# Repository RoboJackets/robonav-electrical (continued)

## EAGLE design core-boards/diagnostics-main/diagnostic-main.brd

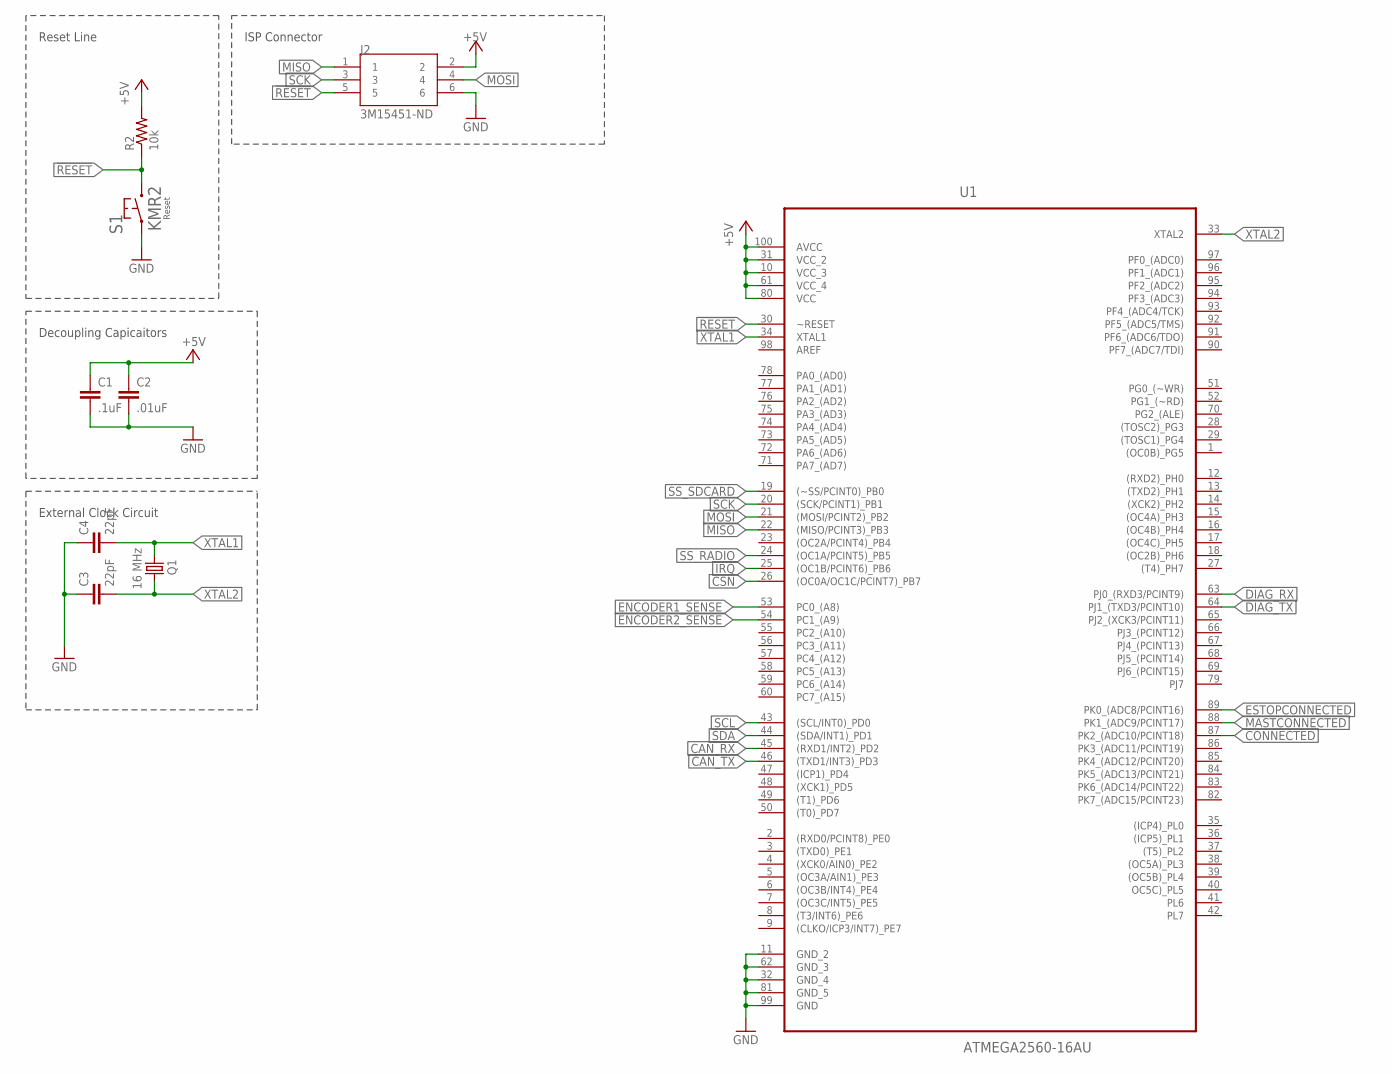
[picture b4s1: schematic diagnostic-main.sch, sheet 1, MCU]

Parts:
C1: .1uF; C0603
C2: .01uF; C0603
C3, C4: 22pF; C0603
J2: 3M15451-ND; 3M_30306-6002HB
Q1: 16 MHz; CSM-7X-DU
R2: 10k; R0402
S1: KMR2
U1: ATMEGA2560-16AU; QFP50P1600X1600X120-100N

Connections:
!RESET: J2.5, R2.1, S1.2.1 (2), S1.2.2 (2), U1.30 (~RESET)
+5V: C1.1, C2.1, J2.2, R2.2, U1.10 (VCC_3), U1.31 (VCC_2), U1.61 (VCC_4), U1.80 (VCC), U1.100 (AVCC); also elsewhere on the board
CAN_RX: U1.45 ((RXD1/INT2)_PD2); also elsewhere on the board
CAN_TX: U1.46 ((TXD1/INT3)_PD3); also elsewhere on the board
CONNECTED: U1.87 (PK2_(ADC10/PCINT18)); also elsewhere on the board
CSN: U1.26 ((OC0A/OC1C/PCINT7)_PB7); also elsewhere on the board
DIAG_RX: U1.63 (PJ0_(RXD3/PCINT9)); also elsewhere on the board
DIAG_TX: U1.64 (PJ1_(TXD3/PCINT10)); also elsewhere on the board
ENCODER1_SENSE: U1.53 (PC0_(A8)); also elsewhere on the board
ENCODER2_SENSE: U1.54 (PC1_(A9)); also elsewhere on the board
ESTOPCONNECTED: U1.89 (PK0_(ADC8/PCINT16)); also elsewhere on the board
GND: C1.2, C2.2, C3.1, C4.1, J2.6, S1.1.1 (1), S1.1.2 (1), U1.11 (GND_2), U1.32 (GND_4), U1.62 (GND_3), U1.81 (GND_5), U1.99 (GND); also elsewhere on the board
IRQ: U1.25 ((OC1B/PCINT6)_PB6); also elsewhere on the board
MASTCONNECTED: U1.88 (PK1_(ADC9/PCINT17)); also elsewhere on the board
MISO: J2.1, U1.22 ((MISO/PCINT3)_PB3); also elsewhere on the board
MOSI: J2.4, U1.21 ((MOSI/PCINT2)_PB2); also elsewhere on the board
SCK: J2.3, U1.20 ((SCK/PCINT1)_PB1); also elsewhere on the board
SCL: U1.43 ((SCL/INT0)_PD0)
SDA: U1.44 ((SDA/INT1)_PD1)
SS_RADIO: U1.24 ((OC1A/PCINT5)_PB5); also elsewhere on the board
SS_SDCARD: U1.19 ((~SS/PCINT0)_PB0); also elsewhere on the board
XTAL1: C4.2, Q1.1, U1.34 (XTAL1)
XTAL2: C3.2, Q1.2, U1.33 (XTAL2)

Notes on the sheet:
Reset Line
External Clock Circuit
Decoupling Capicaitors
ISP Connector

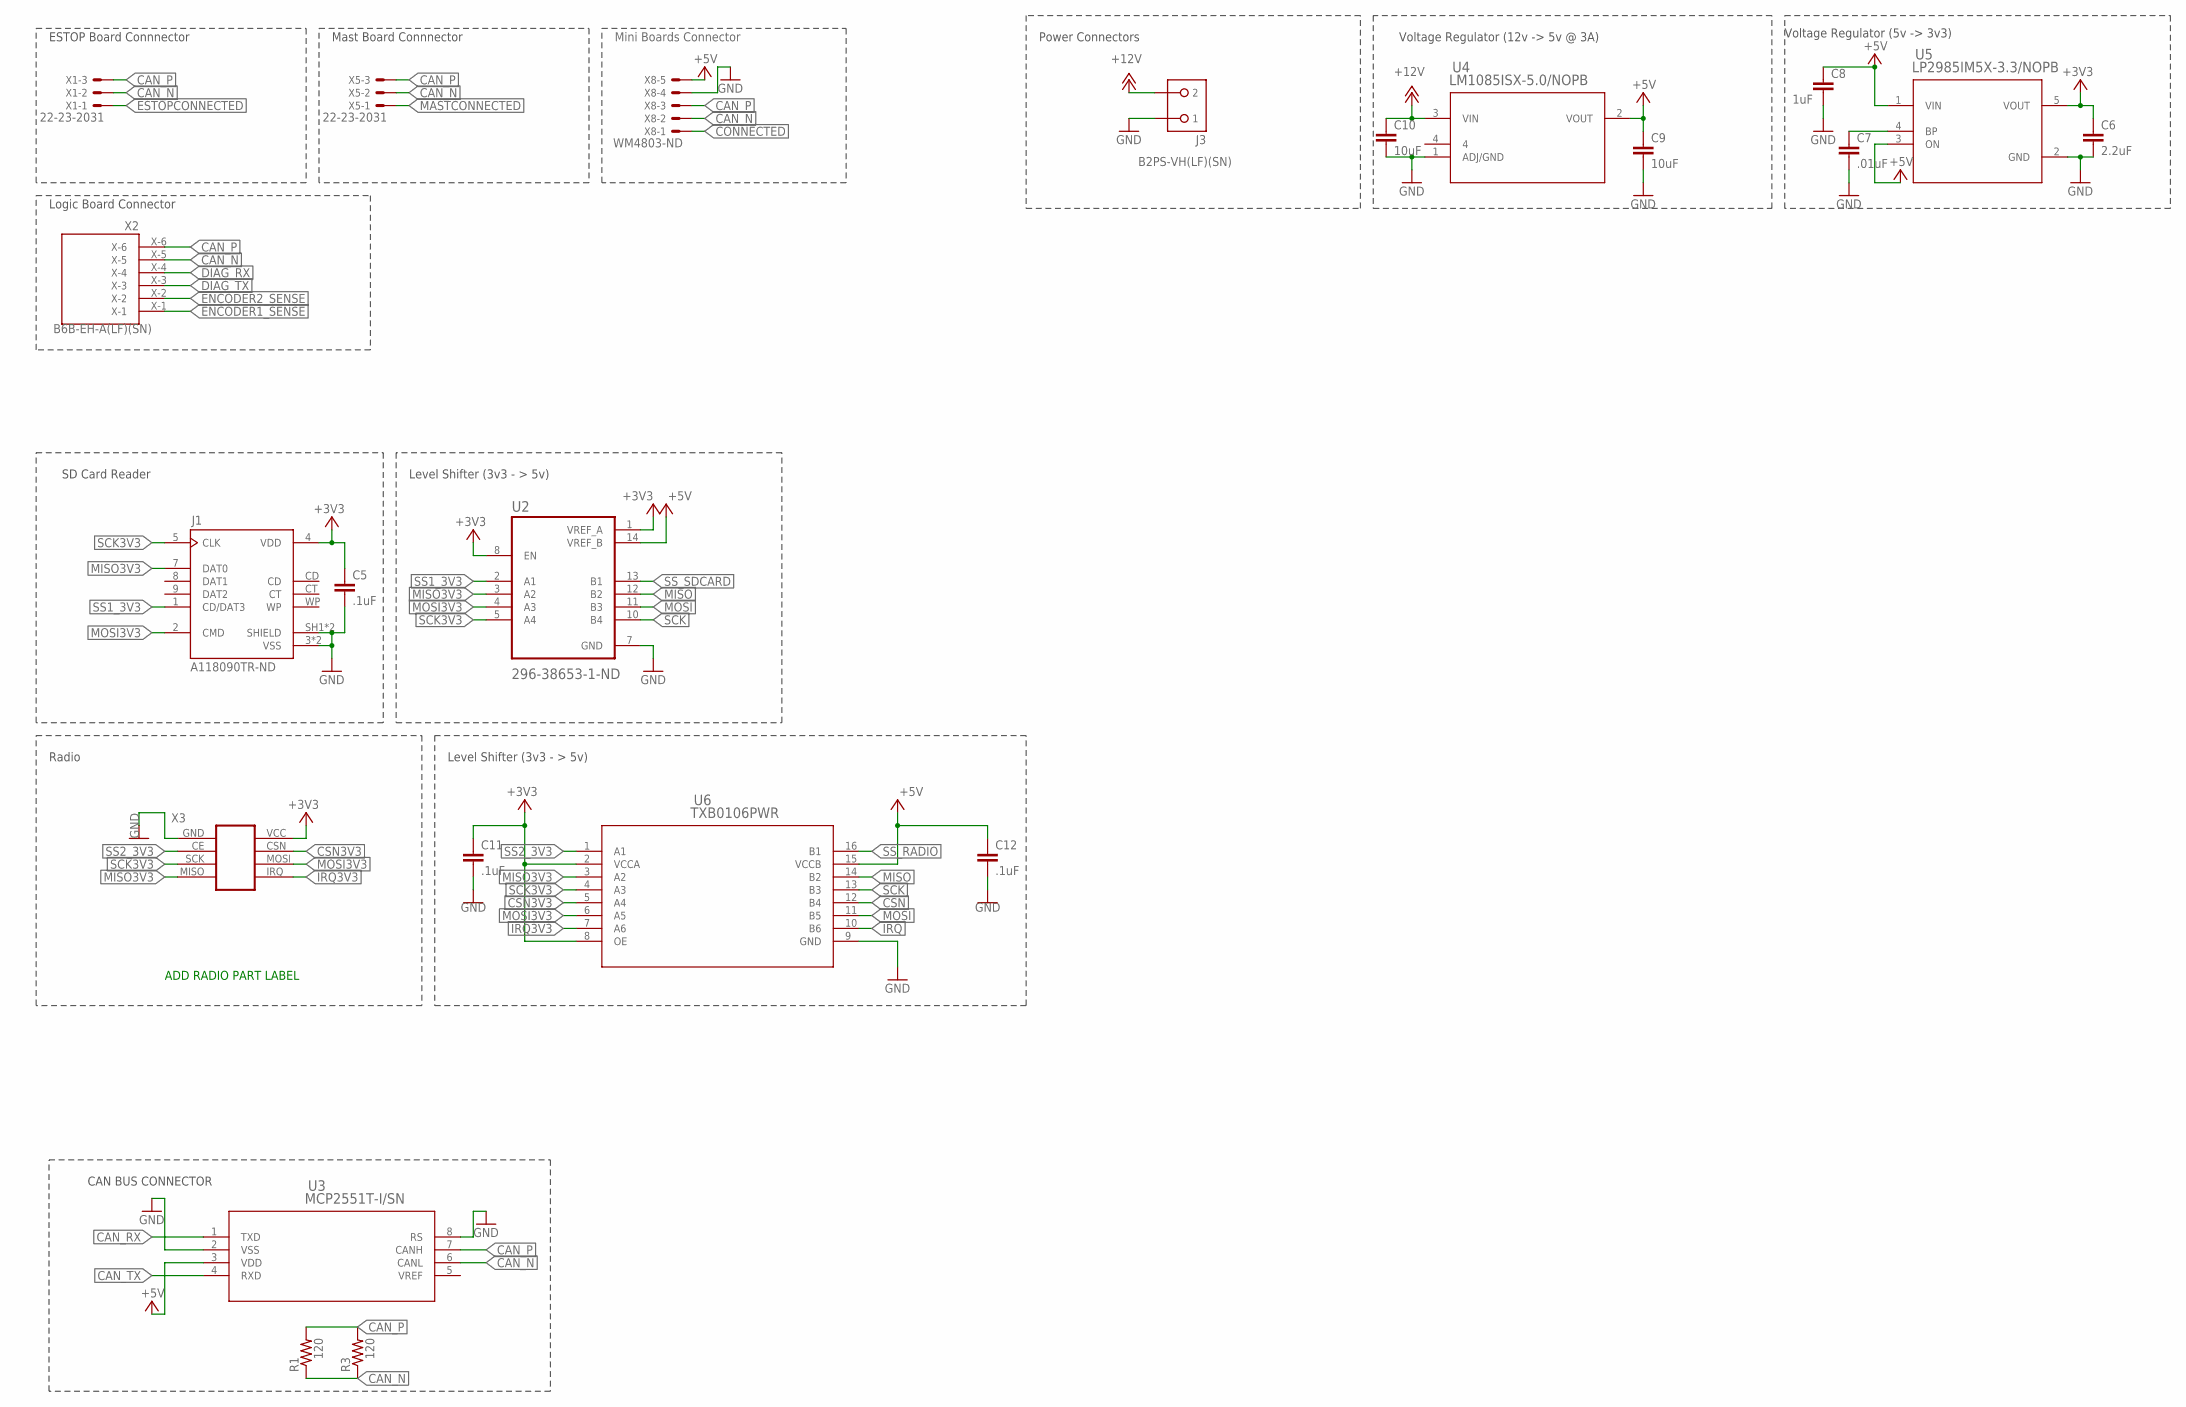
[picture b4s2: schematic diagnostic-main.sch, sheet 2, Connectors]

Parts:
C5, C11, C12: .1uF; C0603
C6: 2.2uF; C0603
C7: .01uF; C0603
C8: 1uF; C0603
C9, C10: 10uF; C0805
J1: A118090TR-ND; TE_1939870-1
J3: B2PS-VH(LF)(SN); B2PS-CENTERED
R1, R3: 120; R0402
U2: 296-38653-1-ND; SOP65P640X120-14N
U3: MCP2551T-I/SN; SOIC8-N_MC
U4: LM1085ISX-5.0/NOPB; TS3B
U5: LP2985IM5X-3.3/NOPB; MF05A
U6: TXB0106PWR; PW16
X1, X5: 22-23-2031
X2: B6B-EH-A(LF)(SN); B6BEHALFSN
X3: NRF24L01+PA+LNA
X8: WM4803-ND; 22-23-2051

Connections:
+3V3: C5.1, C6.1, C11.1, J1.4 (VDD), U2.1 (VREF_A), U2.8 (EN), U5.5 (VOUT), U6.2 (VCCA), U6.8 (OE), X3.VCC
+5V: C8.1, C9.1, C12.1, U2.14 (VREF_B), U3.3 (VDD), U4.2 (VOUT), U5.1 (VIN), U5.3 (ON), U6.15 (VCCB), X8.5; also elsewhere on the board
+12V: C10.1, J3.2, U4.3 (VIN)
CAN_N: R1.1, R3.1, U3.6 (CANL), X1.2, X2.X-5, X5.2, X8.2
CAN_P: R1.2, R3.2, U3.7 (CANH), X1.3, X2.X-6, X5.3, X8.3
CAN_RX: U3.1 (TXD); also elsewhere on the board
CAN_TX: U3.4 (RXD); also elsewhere on the board
CONNECTED: X8.1; also elsewhere on the board
CSN: U6.12 (B4); also elsewhere on the board
CSN3V3: U6.5 (A4), X3.CSN
DIAG_RX: X2.X-4; also elsewhere on the board
DIAG_TX: X2.X-3; also elsewhere on the board
ENCODER1_SENSE: X2.X-1; also elsewhere on the board
ENCODER2_SENSE: X2.X-2; also elsewhere on the board
ESTOPCONNECTED: X1.1; also elsewhere on the board
GND: C5.2, C6.2, C7.2, C8.2, C9.2, C10.2, C11.2, C12.2, J1.3 (VSS), J1.6 (VSS), J1.SH1 (SHIELD), J1.SH2 (SHIELD), J3.1, U2.7 (GND), U3.2 (VSS), U3.8 (RS), U4.1 (ADJ/GND), U5.2 (GND), U6.9 (GND), X3.GND, X8.4; also elsewhere on the board
IRQ: U6.10 (B6); also elsewhere on the board
IRQ3V3: U6.7 (A6), X3.IRQ
MASTCONNECTED: X5.1; also elsewhere on the board
MISO: U2.12 (B2), U6.14 (B2); also elsewhere on the board
MISO3V3: J1.7 (DAT0), U2.3 (A2), U6.3 (A2), X3.MISO
MOSI: U2.11 (B3), U6.11 (B5); also elsewhere on the board
MOSI3V3: J1.2 (CMD), U2.4 (A3), U6.6 (A5), X3.MOSI
unnamed: C7.1, U5.4 (BP)
SCK: U2.10 (B4), U6.13 (B3); also elsewhere on the board
SCK3V3: J1.5 (CLK), U2.5 (A4), U6.4 (A3), X3.SCK
SS1_3V3: J1.1 (CD/DAT3), U2.2 (A1)
SS2_3V3: U6.1 (A1), X3.CE
SS_RADIO: U6.16 (B1); also elsewhere on the board
SS_SDCARD: U2.13 (B1); also elsewhere on the board

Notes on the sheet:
ESTOP Board Connnector
SD Card Reader
Level Shifter (3v3 - > 5v)
Logic Board Connector
Mini Boards Connector
CAN BUS CONNECTOR
Voltage Regulator (12v -> 5v @ 3A)
Voltage Regulator (5v -> 3v3)
Power Connectors
Radio
Mast Board Connnector
ADD RADIO PART LABEL

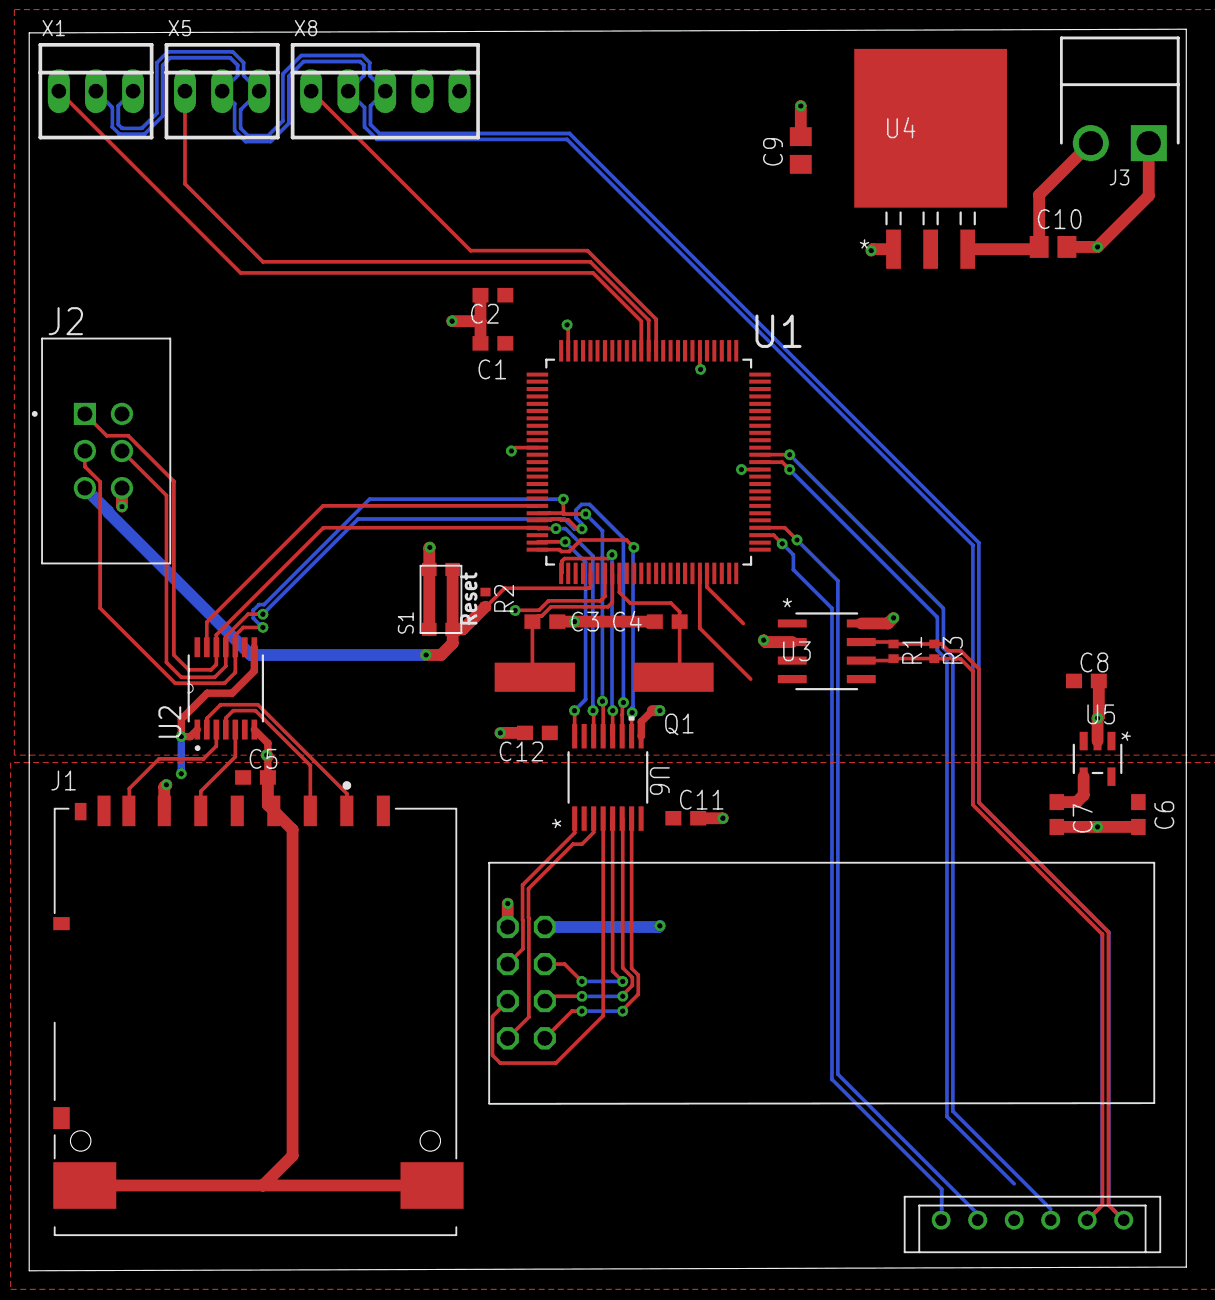
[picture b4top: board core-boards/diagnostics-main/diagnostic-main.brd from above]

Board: 2 copper layers, 79.2 x 85.0 mm, 31 parts (0 on the bottom side), 33 nets.

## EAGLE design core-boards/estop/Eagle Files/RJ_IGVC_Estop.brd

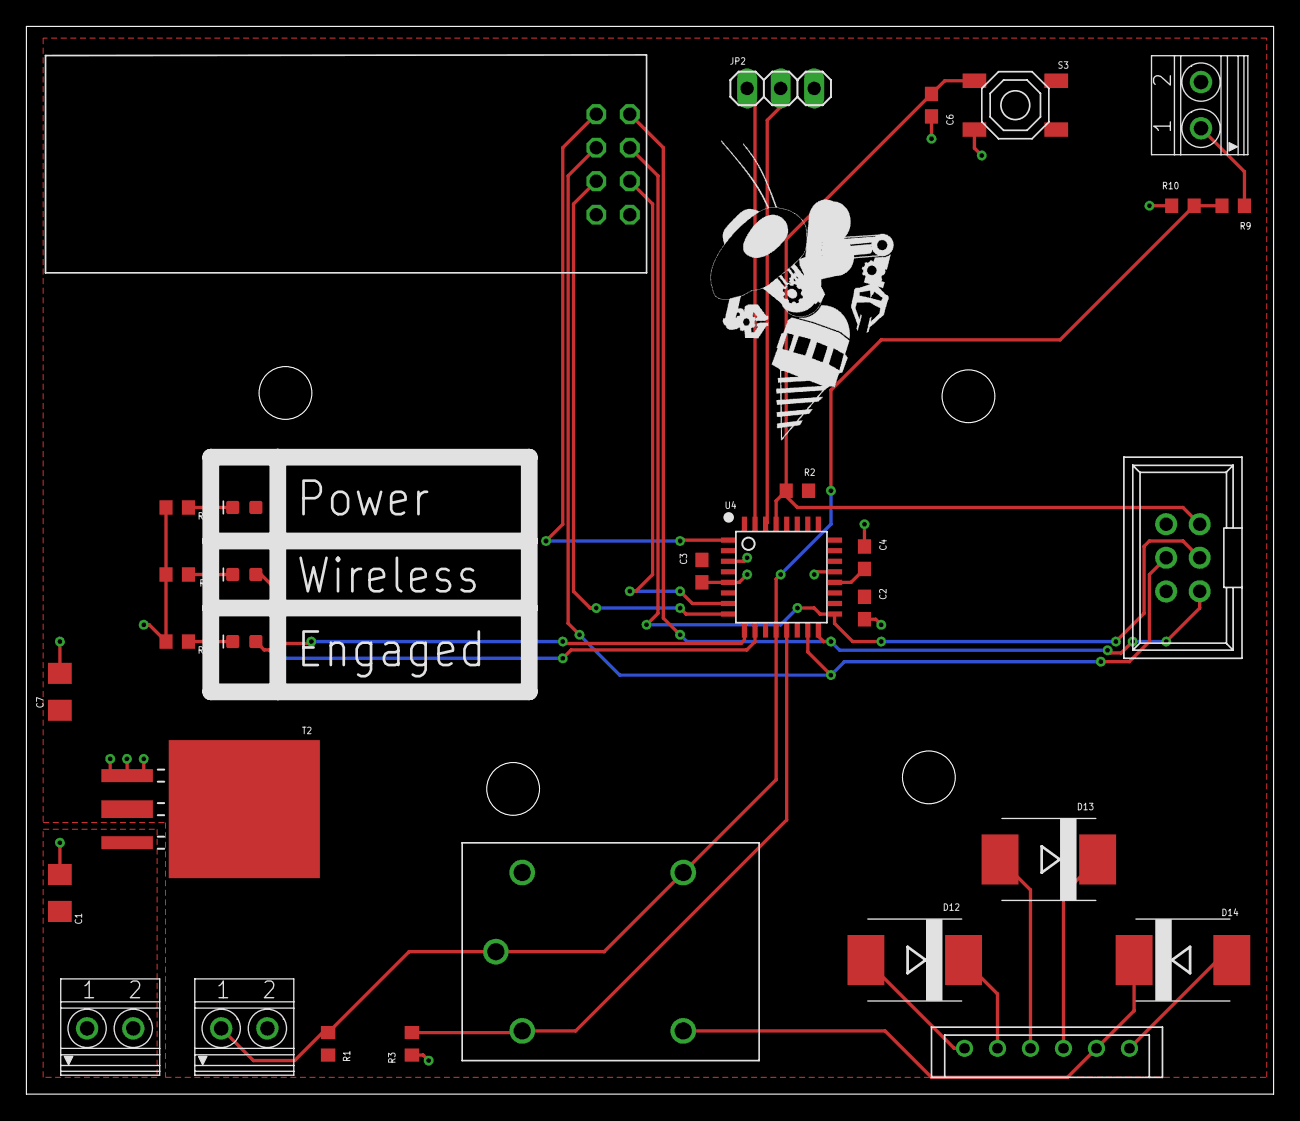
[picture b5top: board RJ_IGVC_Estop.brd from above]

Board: 2 copper layers, 94.5 x 80.9 mm, 32 parts (0 on the bottom side), 26 nets.

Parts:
C1, C7: 10uF; C1206
C2, C3, C4, C6: 0.1uF; C0603
D1, D2, D3: Green; LED-0603
D12, D13, D14: S10M-TP; SMC
JP2: Serial; 1X03
PROG: ICSP Connector; 2X3SHROUDED
R1, R2, R3: 10k; R0603
R4, R5, R6: 1k; R0603
R9: 4.7k; R0603
R10: 750; R0603
S3: SKQGADE010; SW4-SMD-5.2X5.2X1.5MM
T2: LD1086D2M33TR; D2PAK/A
U4: ATMEGA328P-AUR
U$1: G5LE-14
U$2: ROBOBUZZ_1.2X
X2: Power; 1751248
X3: Button In; 1751248
X4: E-Stop Signal In; 1751248
X5: NRF24L01+PA+LNA
X6: B6B-EH-A(LF)(SN); B6BEHALFSN

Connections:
!RESET: C6.1, PROG.!RESET, R2.1, S3.1, U4.29
+3V3: C2.1, C3.1, C7.1, D2.A, PROG.+5V, R1.1, R2.2, T2.2, U4.4, U4.6, U4.18, X5.VCC
+24V: D12.A, X6.X-1
BUTTON_LED: D1.A, U4.9
CE: U4.7, X5.CE
CSN: U4.8, X5.CSN
DIODE_TO_GREEN: D12.C, X6.X-2
DIODE_TO_INTER: D13.C, X6.X-4
GND: C1.2, C2.2, C3.2, C4.2, C6.2, C7.2, D14.A, JP2.3, PROG.GND, R3.1, R4.1, R5.1, R6.1, R10.2, S3.4, T2.1, U4.3, U4.5, U4.21, U$1.P$1, X2.2, X3.2, X4.2, X5.GND, X6.X-6
IN: R1.2, R9.2, R10.1, U4.12, U$1.P$2, U$1.P$4, X3.1
IRQ: U4.1, X5.IRQ
MISO: PROG.MISO, U4.16, X5.MISO
MOSI: PROG.MOSI, U4.15, X5.MOSI
MOTOR_POWER: D13.A, X6.X-3
unnamed: D2.C, R5.2
unnamed: D1.C, R4.2
unnamed: D3.C, R6.2
unnamed: R9.1, X4.1
unnamed: C4.1, U4.20
OUT: R3.2, U4.13, U$1.P$3
RX: JP2.2, U4.30
SCK: PROG.SCK, U4.17, X5.SCK
SOLENOID_TRIG: D14.C, U$1.P$5, X6.X-5
TX: JP2.1, U4.31
V_IN: C1.1, T2.3, X2.1
WIRELESS_LED: D3.A, U4.10

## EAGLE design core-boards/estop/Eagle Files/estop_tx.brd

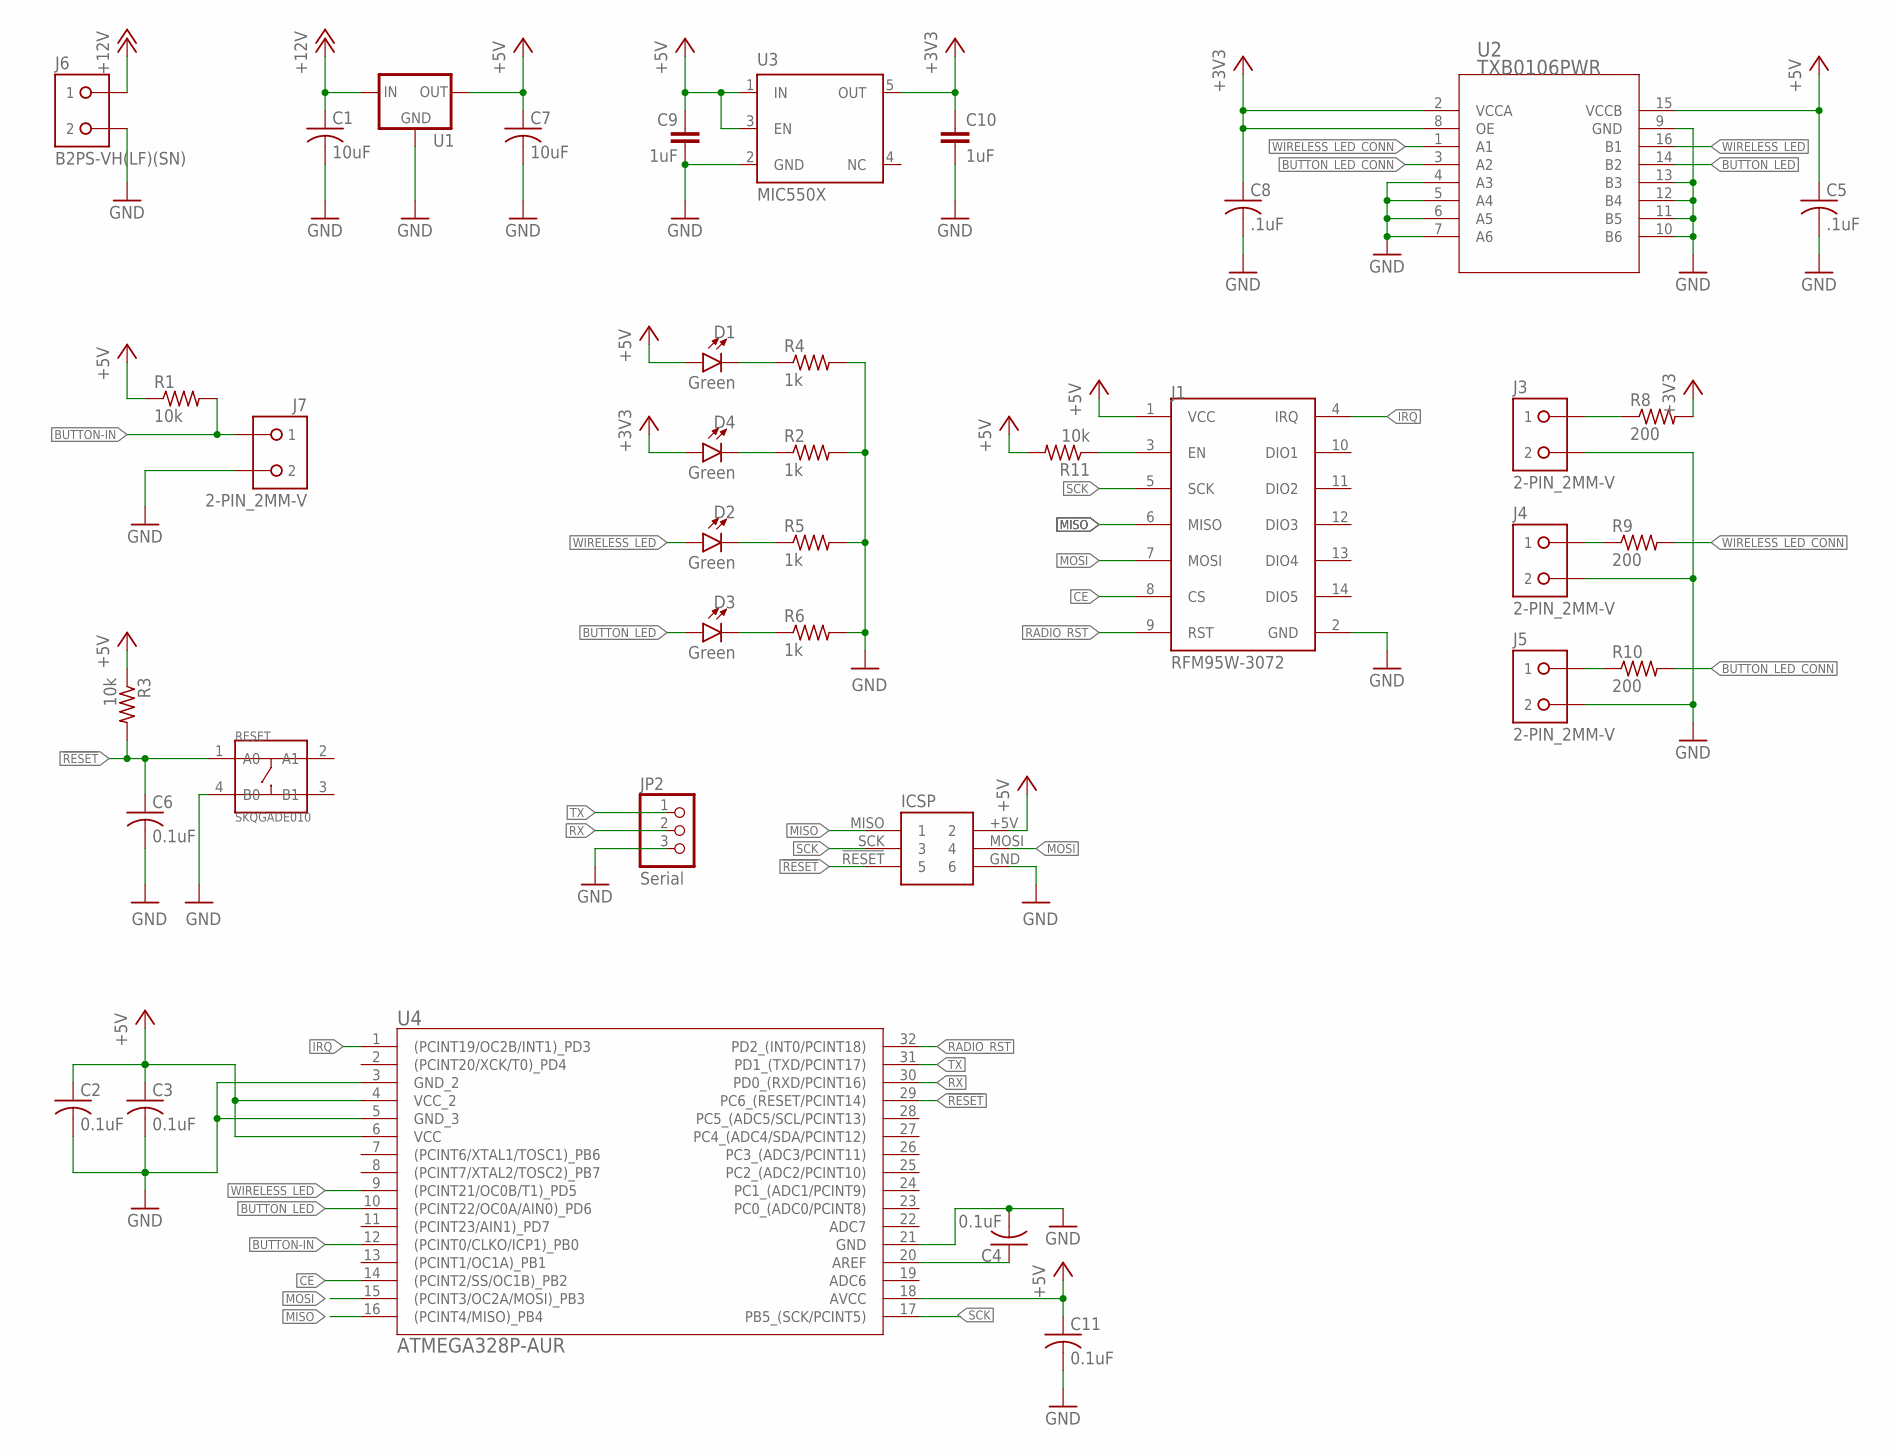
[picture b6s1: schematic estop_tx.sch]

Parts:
C1, C7: 10uF; C0805
C2, C3, C4, C6, C11: 0.1uF; C0603
C5, C8: .1uF; C0603
C9, C10: 1uF; C0603
D1, D2, D3, D4: Green; LED-0603
ICSP: ICSP Connector; 2X3SHROUDED
J1: RFM95W-3072
J3, J4, J5, J7: 2-PIN_2MM-V; 2MM-2-V
J6: B2PS-VH(LF)(SN); B2PS-CENTERED
JP2: Serial; 1X03
R1, R3, R11: 10k; R0603
R2, R4, R5, R6: 1k; R0603
R8, R9, R10: 200; R0603
RESET: SKQGADE010; SW4-SMD-5.2X5.2X1.5MM
U1: R-78E5.0-1.0CONV_R-78E5.0-1.0; CONV_R-78E5.0-1.0
U2: TXB0106PWR; PW16
U3: MIC550X; SOT23-DBV
U4: ATMEGA328P-AUR

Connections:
!RESET: C6.1, ICSP.!RESET (5), R3.2, RESET.1 (A0), U4.29 (PC6_(RESET/PCINT14))
+3V3: C8.1, C10.1, D4.A, R8.2, U2.2 (VCCA), U2.8 (OE), U3.5 (OUT)
+5V: C2.1, C3.1, C5.1, C7.1, C9.1, C11.1, D1.A, ICSP.+5V (2), J1.1 (VCC), R1.1, R3.1, R11.2, U1.3 (OUT), U2.15 (VCCB), U3.1 (IN), U3.3 (EN), U4.4 (VCC_2), U4.6 (VCC), U4.18 (AVCC)
+12V: C1.1, J6.1, U1.1 (IN)
BUTTON-IN: J7.1, R1.2, U4.12 ((PCINT0/CLKO/ICP1)_PB0)
BUTTON_LED: D3.A, U2.14 (B2), U4.10 ((PCINT22/OC0A/AIN0)_PD6)
BUTTON_LED_CONN: R10.2, U2.3 (A2)
CE: J1.8 (CS), U4.14 ((PCINT2/SS/OC1B)_PB2)
EN: J1.3 (EN), R11.1
GND: C1.2, C2.2, C3.2, C4.2, C5.2, C6.2, C7.2, C8.2, C9.2, C10.2, C11.2, ICSP.GND (6), J1.2 (GND), J3.2, J4.2, J5.2, J6.2, J7.2, JP2.3, R2.2, R4.2, R5.2, R6.2, RESET.4 (B0), U1.2 (GND), U2.4 (A3), U2.5 (A4), U2.6 (A5), U2.7 (A6), U2.9 (GND), U2.10 (B6), U2.11 (B5), U2.12 (B4), U2.13 (B3), U3.2 (GND), U4.3 (GND_2), U4.5 (GND_3), U4.21 (GND)
IRQ: J1.4 (IRQ), U4.1 ((PCINT19/OC2B/INT1)_PD3)
MISO: ICSP.MISO (1), J1.6 (MISO), U4.16 ((PCINT4/MISO)_PB4)
MOSI: ICSP.MOSI (4), J1.7 (MOSI), U4.15 ((PCINT3/OC2A/MOSI)_PB3)
unnamed: J3.1, R8.1
unnamed: D1.C, R4.1
unnamed: D3.C, R6.1
unnamed: D2.C, R5.1
unnamed: D4.C, R2.1
unnamed: J4.1, R9.1
unnamed: J5.1, R10.1
unnamed: C4.1, U4.20 (AREF)
RADIO_RST: J1.9 (RST), U4.32 (PD2_(INT0/PCINT18))
RX: JP2.2, U4.30 (PD0_(RXD/PCINT16))
SCK: ICSP.SCK (3), J1.5 (SCK), U4.17 (PB5_(SCK/PCINT5))
TX: JP2.1, U4.31 (PD1_(TXD/PCINT17))
WIRELESS_LED: D2.A, U2.16 (B1), U4.9 ((PCINT21/OC0B/T1)_PD5)
WIRELESS_LED_CONN: R9.2, U2.1 (A1)

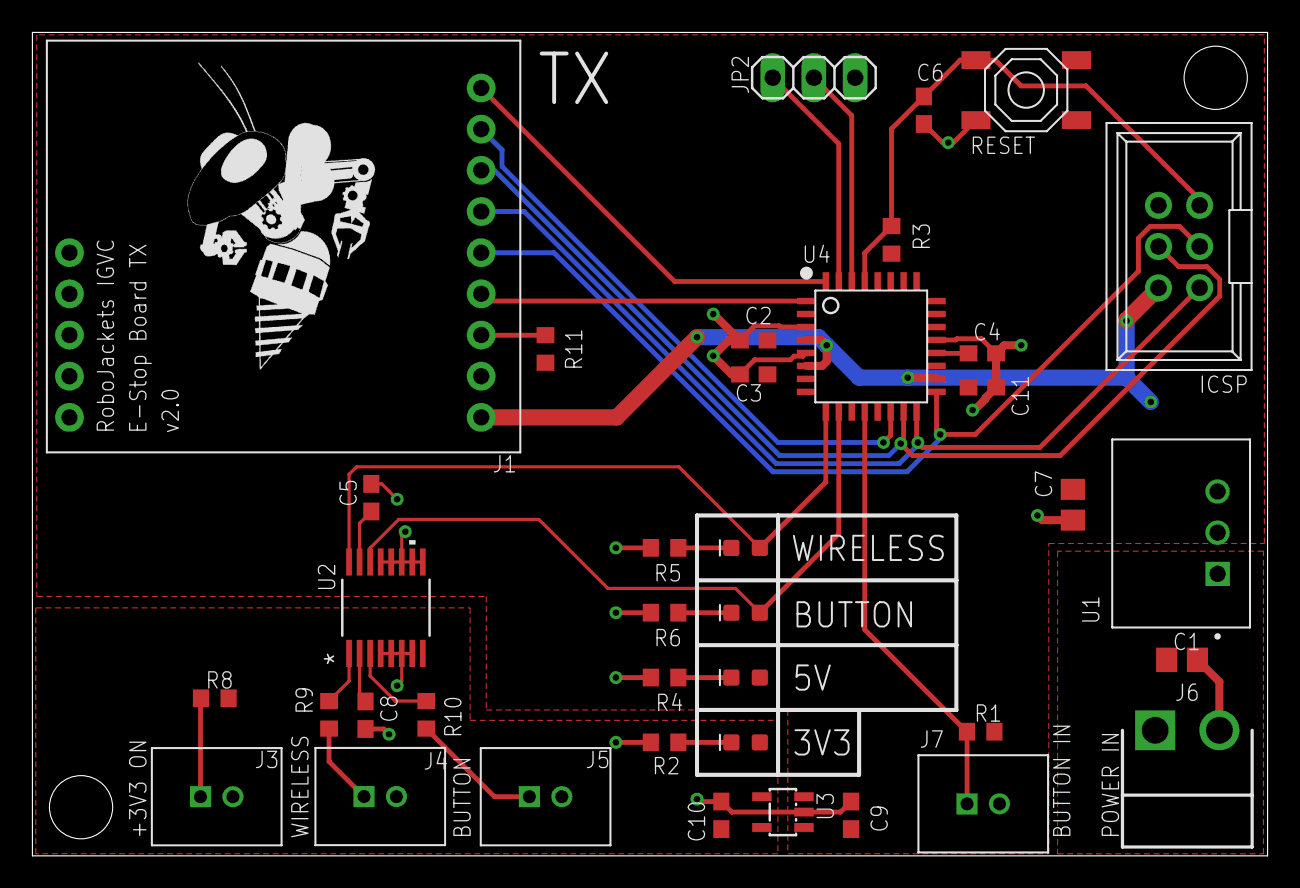
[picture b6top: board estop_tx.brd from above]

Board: 2 copper layers, 76.2 x 50.8 mm, 41 parts (0 on the bottom side), 27 nets.

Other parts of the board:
U$1: ROBOBUZZ_1.0X
U$2, U$3: STANDOFF-HOLE

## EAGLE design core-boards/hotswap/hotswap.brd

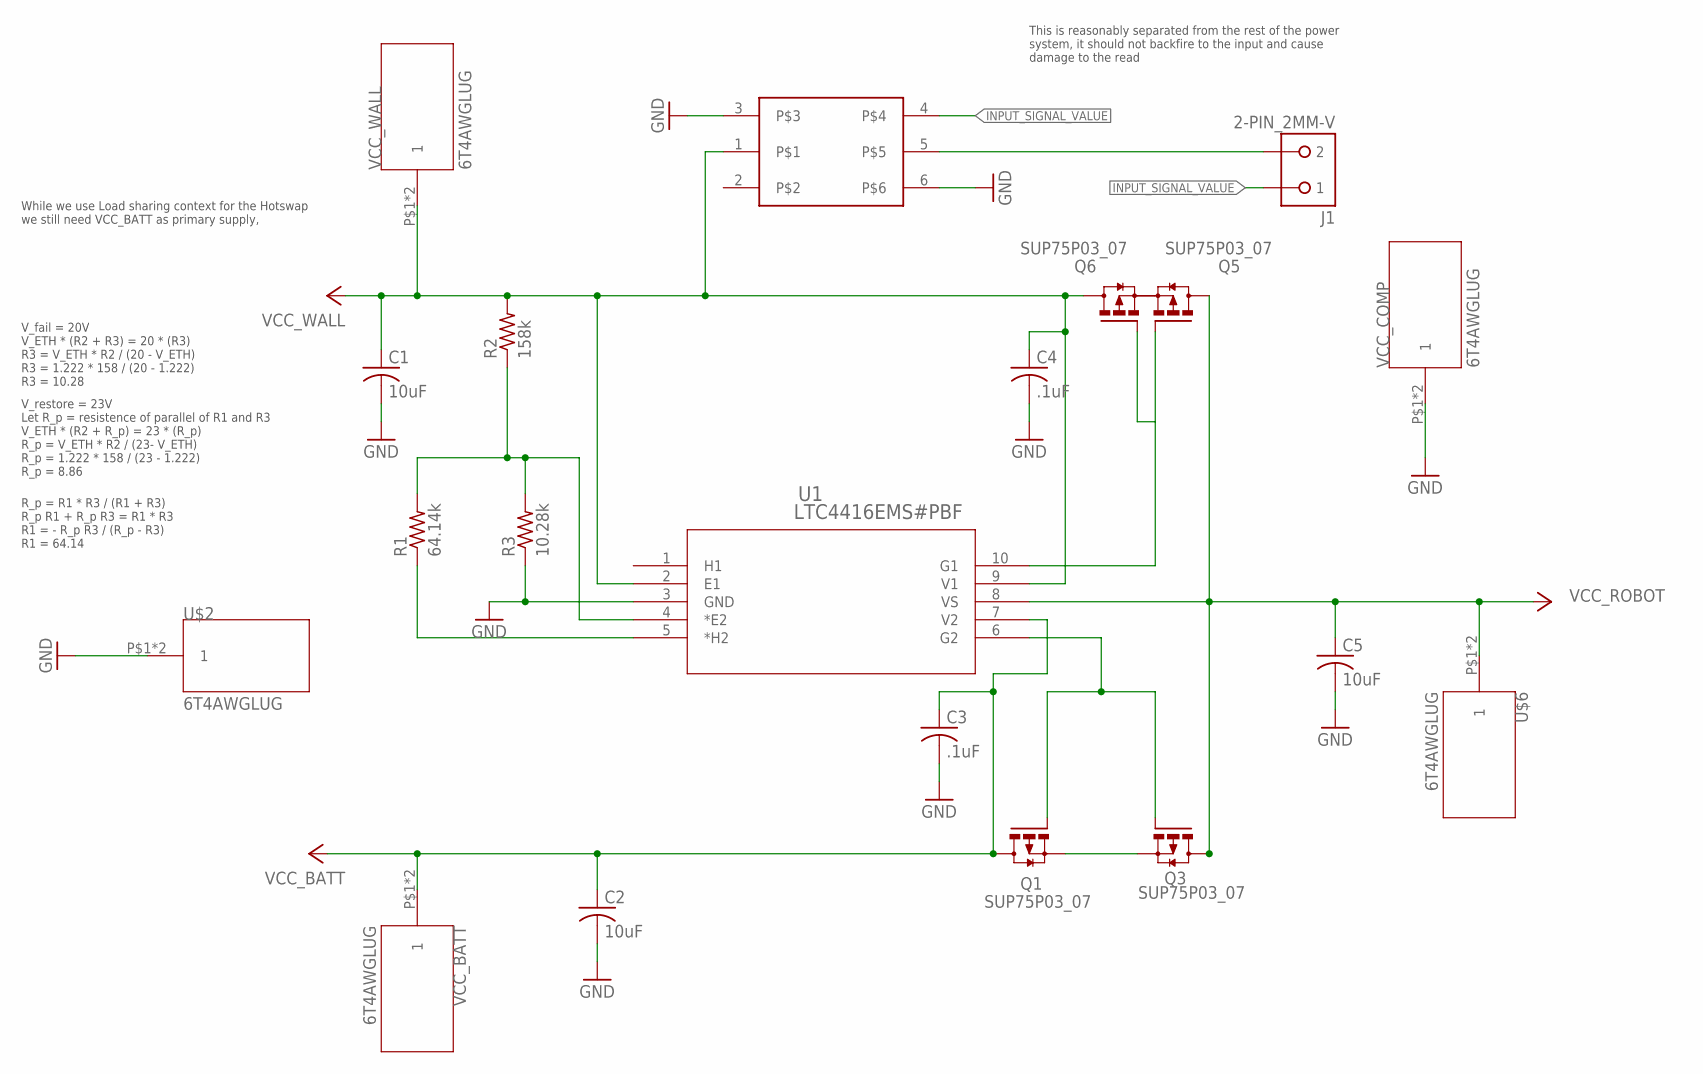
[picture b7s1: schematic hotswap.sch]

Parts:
C1, C2, C5: 10uF; C1210
C3, C4: .1uF; C0805
J1: 2-PIN_2MM-V; 2MM-2-V
Q1, Q3, Q5, Q6: SUP75P03_07; DPACK_2
R1: 64.14k; R0603
R2: 158k; R0603
R3: 10.28k; R0603
U1: LTC4416EMS#PBF; MSOP-10_MS
U$2, U$6: 6T4AWGLUG
VCC_BATT: 6T4AWGLUG
VCC_COMP: 6T4AWGLUG
VCC_WALL: 6T4AWGLUG
Z1: TLP2745

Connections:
GND: C1.2, C2.2, C3.2, C4.2, C5.2, R3.1, U1.3 (GND), U$2.P$1, U$2.P$2, VCC_COMP.P$1, VCC_COMP.P$2, Z1.3, Z1.6
INPUT_SIGNAL_VALUE: J1.1, Z1.4
unnamed: Q1.S, Q3.S
unnamed: Q1.G, Q3.G, U1.6 (G2)
unnamed: Q5.G, Q6.G, U1.10 (G1)
unnamed: R1.2, R2.1, R3.2, U1.4 (*E2)
unnamed: J1.2, Z1.5
unnamed: R1.1, U1.5 (*H2)
VCC_BATT: C2.1, C3.1, Q1.D, U1.7 (V2), VCC_BATT.P$1, VCC_BATT.P$2
VCC_ROBOT: C5.1, Q3.D, Q5.D, U1.8 (VS), U$6.P$1, U$6.P$2
VCC_WALL: C1.1, C4.1, Q6.D, R2.2, U1.2 (E1), U1.9 (V1), VCC_WALL.P$1, VCC_WALL.P$2, Z1.1

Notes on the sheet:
This is reasonably separated from the rest of the power system, it should not backfire to the input and cause damage to the read
While we use Load sharing context for the Hotswap we still need VCC_BATT as primary supply,
V_fail = 20V V_ETH * (R2 + R3) = 20 * (R3) R3 = V_ETH * R2 / (20 - V_ETH) R3 = 1.222 * 158 / (20 - 1.222) R3 = 10.28
V_restore = 23V Let R_p = resistence of parallel of R1 and R3 V_ETH * (R2 + R_p) = 23 * (R_p) R_p = V_ETH * R2 / (23- V_ETH) R_p = 1.222 * 158 / (23 - 1.222) R_p = 8.86
R_p = R1 * R3 / (R1 + R3) R_p R1 + R_p R3 = R1 * R3 R1 = - R_p R3 / (R_p - R3) R1 = 64.14

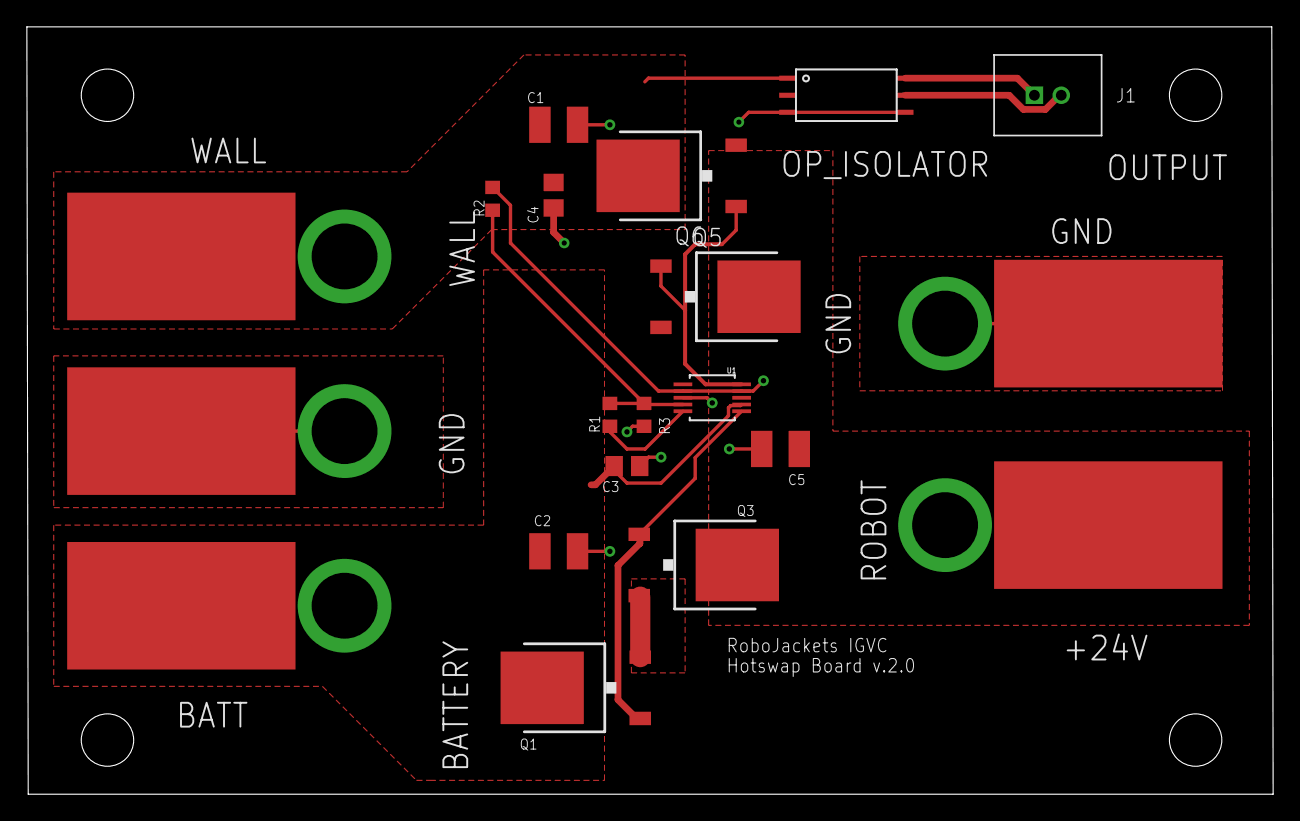
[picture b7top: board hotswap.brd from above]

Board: 2 copper layers, 92.8 x 57.1 mm, 25 parts (1 on the bottom side), 11 nets.

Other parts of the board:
E$1: ROBOBUZZ_0.8X
U$3, U$4, U$5, U$7: STANDOFF-HOLE
